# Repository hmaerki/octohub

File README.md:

# octohub

A simple usb 2.0 hub with focus on per port power switching.

Work in progress.

## Features - Hardware

* ~USD 4 when ordering 30 pieces. Fully assembled at JLCPCB.

* Kicad. Production files ready to upload to JLCPCB.

* Power control for each plug using (uhubctl)[https://github.com/mvp/uhubctl].

* **NO** manual power buttons. Many commercial hubs have buttons. If accidentely pressed, usb switching is disabled.

* Power LEDs which are visible from different angles. Many commercial switchs have LEDs, but not well visible.

* Plug numbering. Many commercial switches do not number the plugs and there is very little space left to add stickers.

## Features - Electronics

USB2 only. This makes `uhubctl` much faster.

Bus powered. Less cables is better.

USB descripter `self-powered`. This is against the USB spec. This is required as a RP2 requests 500mA. The USB 2.0 spec allows a bus-powered device to use max 100mA. The current measureed on the RP2 is only 25mA.

Over current protection. However, no over current feedback to USB.

If a device requires USB3, it is still possible to use a commercial hub.

## Current state of v0.2:

[Schematics](octohub_kicad_v0.2/production_v0.2/schematics.pdf)

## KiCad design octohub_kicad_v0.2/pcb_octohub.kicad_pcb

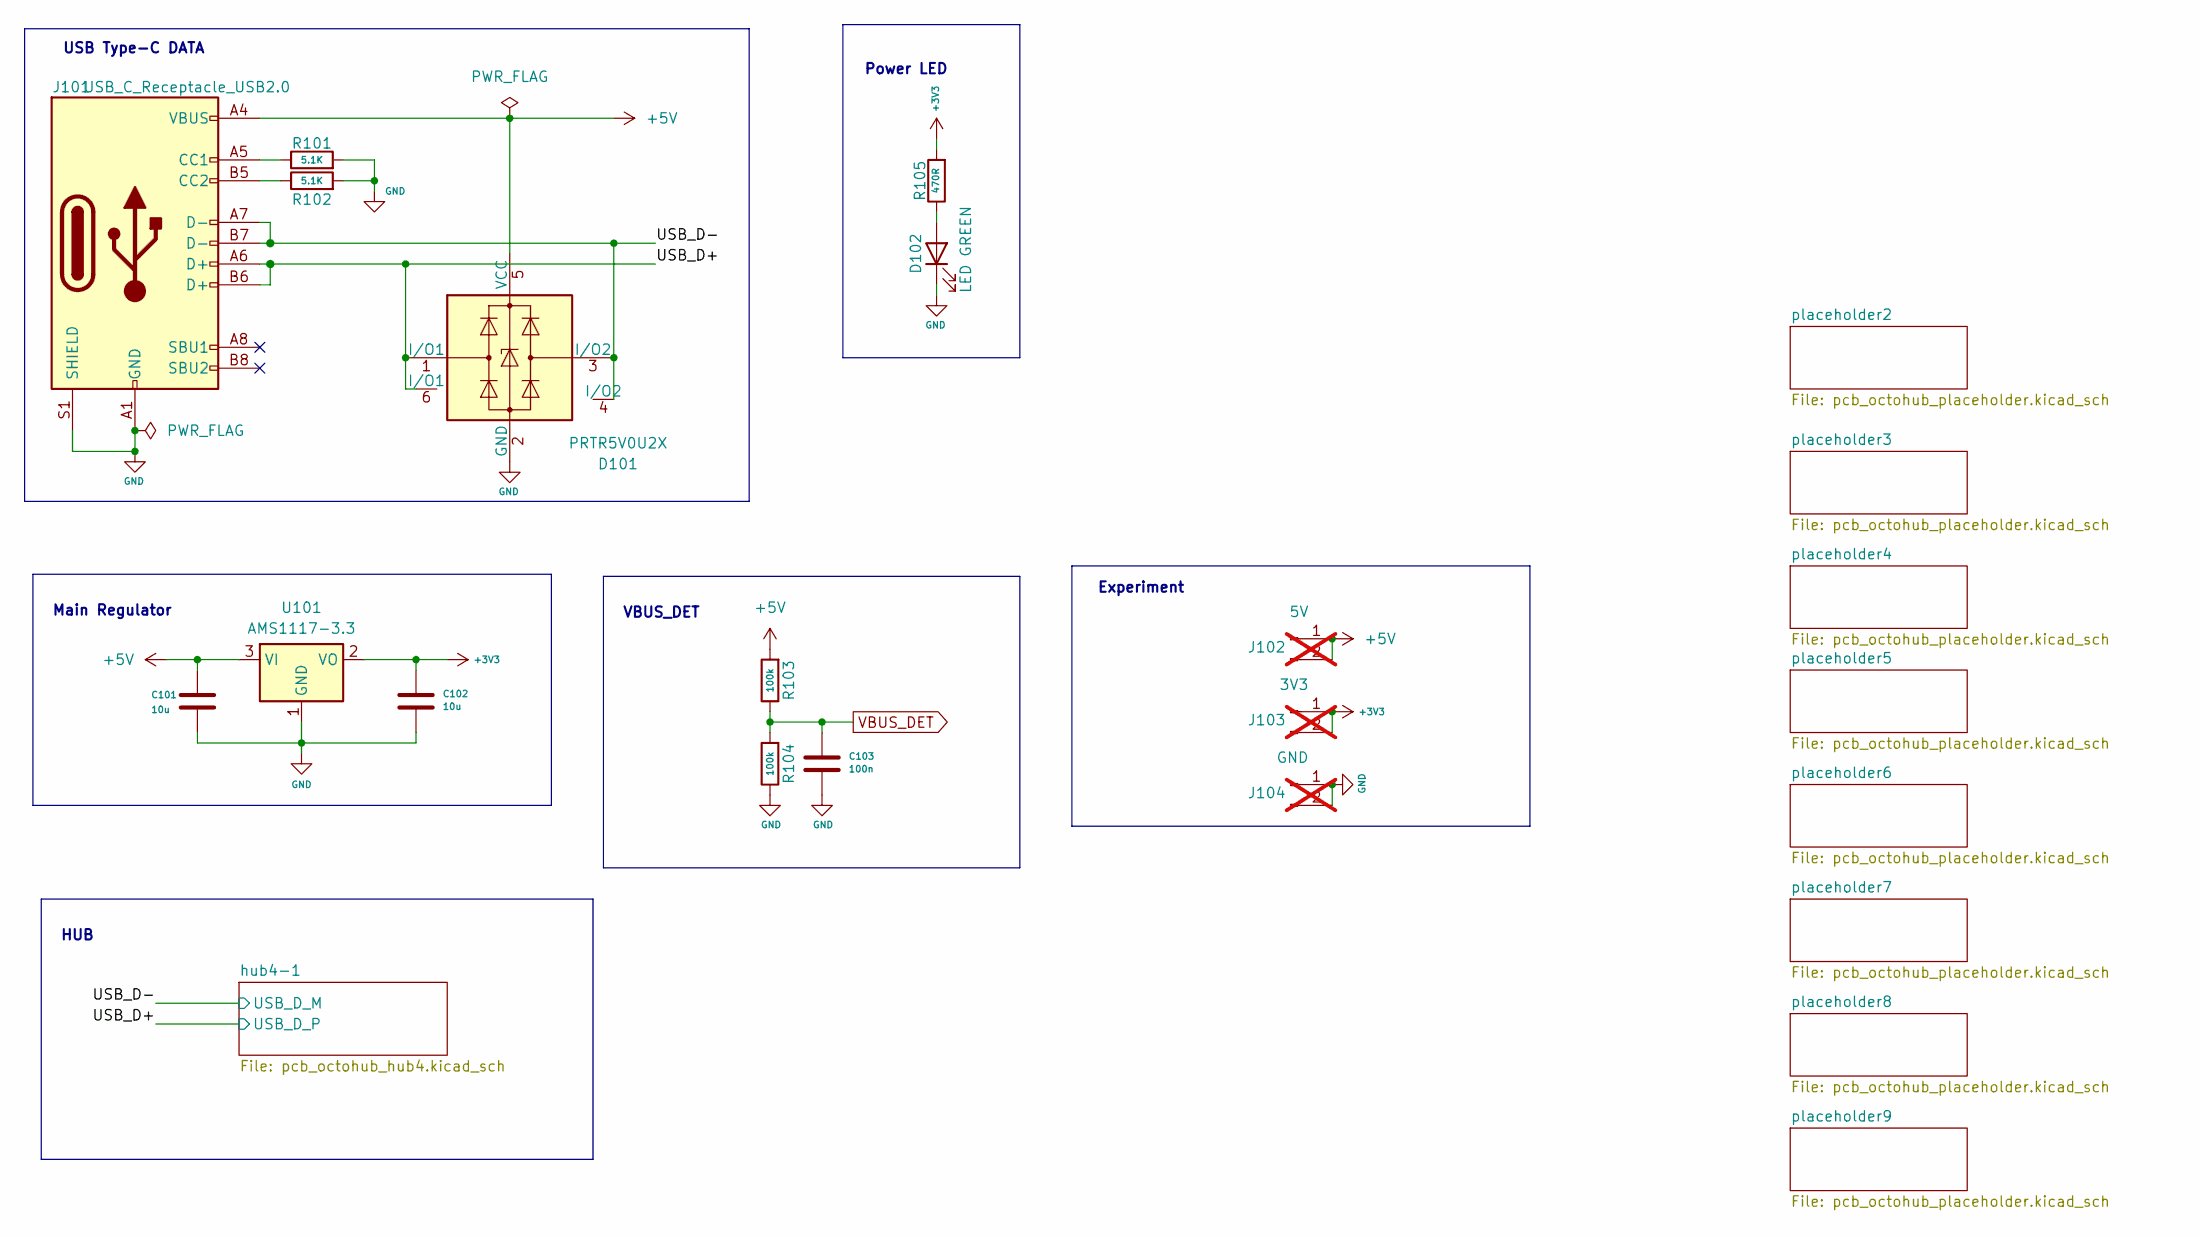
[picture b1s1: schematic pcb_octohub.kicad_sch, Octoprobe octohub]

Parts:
C101, C102: 10u; C_0603_1608Metric
C103: 100n; C_0603_1608Metric
D101: PRTR5V0U2X; Texas_USON-6_1x1.45mm_P0.5mm_SMD; JLC C2937001
D102: LED GREEN; LED_0603_1608Metric; JLC C2297
J101: USB_C_Receptacle_USB2.0; USB_C_Receptacle_Palconn_UTC16-G; JLC C165948
J102: 5V; PinHeader_1x02_P2.54mm_Vertical; not fitted
J103: 3V3; PinHeader_1x02_P2.54mm_Vertical; not fitted
J104: GND; PinHeader_1x02_P2.54mm_Vertical; not fitted
R101, R102: 5.1K; R_0402_1005Metric
R103, R104: 100k; R_0402_1005Metric
R105: 470R; R_0402_1005Metric
U101: AMS1117-3.3; SOT-223-3_TabPin2; JLC C6186

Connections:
+3V3: C102.1, J103.1, J103.2, R105.2, U101.2 (VO); also elsewhere on the board
+5V: C101.1, D101.5 (VCC), J101.A4 (VBUS), J101.A9 (VBUS), J101.B4 (VBUS), J101.B9 (VBUS), J102.1, J102.2, R103.2, U101.3 (VI); also elsewhere on the board
/USB_D+: D101.1 (I/O1), D101.6 (I/O1), J101.A6 (D+), J101.B6 (D+); also elsewhere on the board
/USB_D-: D101.3 (I/O2), D101.4 (I/O2), J101.A7 (D-), J101.B7 (D-); also elsewhere on the board
GND: C101.2, C102.2, C103.2, D101.2 (GND), D102.1 (K), J101.A1 (GND), J101.A12 (GND), J101.B1 (GND), J101.B12 (GND), J101.S1 (SHIELD), J104.1, J104.2, R101.2, R102.2, R104.1, U101.1 (GND); also elsewhere on the board
unnamed: D102.2 (A), R105.1
unnamed: J101.A5 (CC1), R101.1
unnamed: J101.B5 (CC2), R102.1
VBUS_DET: C103.1, R103.1, R104.2; also elsewhere on the board

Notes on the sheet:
USB Type-C DATA
VBUS_DET
Power LED
Main Regulator
HUB
Experiment

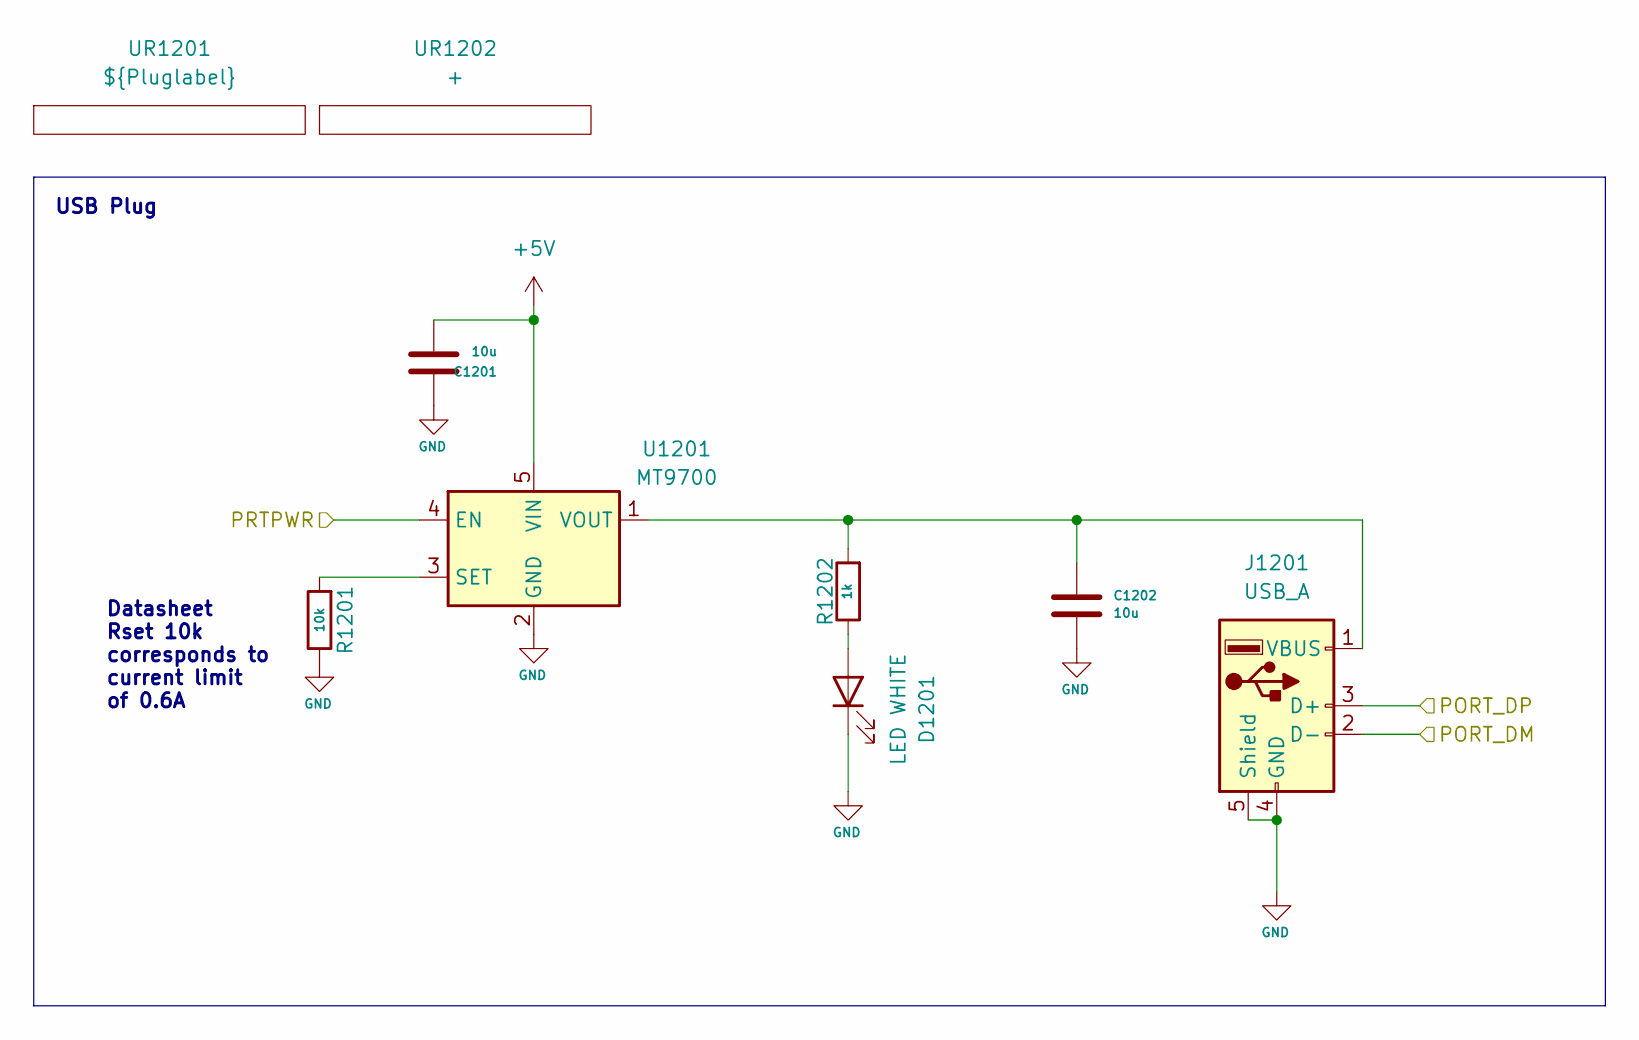
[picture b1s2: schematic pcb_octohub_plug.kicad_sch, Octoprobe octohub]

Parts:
C1201, C1202: 10u; C_0603_1608Metric
D1201: LED WHITE; LED_0603_1608Metric; JLC C2290
J1201: USB_A; USB_A_SHOUHAN_Vertical; JLC C456015
R1201: 10k; R_0402_1005Metric
R1202: 1k; R_0402_1005Metric
U1201: MT9700; SOT-23-5; JLC C89855
UR1201: ${Pluglabel}; octohub_plug_label
UR1202: +; octohub_plug_top_left

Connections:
+5V: C1201.2, U1201.5 (VIN); also elsewhere on the board
/hub4-1/chip_downstream/PRT_D_M1: J1201.2 (D-); also elsewhere on the board
/hub4-1/chip_downstream/PRT_D_P1: J1201.3 (D+); also elsewhere on the board
/hub4-1/chip_downstream/PRT_PWR1: U1201.4 (EN); also elsewhere on the board
GND: C1201.1, C1202.2, D1201.1 (K), J1201.4 (GND), J1201.5 (Shield), R1201.1, U1201.2 (GND); also elsewhere on the board
unnamed: D1201.2 (A), R1202.1
unnamed: C1202.1, J1201.1 (VBUS), R1202.2, U1201.1 (VOUT)
unnamed: R1201.2, U1201.3 (SET)

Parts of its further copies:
C1301, C1302, C1401, C1402, C1501, C1502: 10u; C_0603_1608Metric
D1301, D1401, D1501: LED WHITE; LED_0603_1608Metric; JLC C2290
J1301, J1401, J1501: USB_A; USB_A_SHOUHAN_Vertical; JLC C456015
R1301, R1401, R1501: 10k; R_0402_1005Metric
R1302, R1402, R1502: 1k; R_0402_1005Metric
U1301, U1401, U1501: MT9700; SOT-23-5; JLC C89855
UR1302, UR1402, UR1502: +; octohub_plug_top_left

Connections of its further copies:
+5V: C1301.2, C1401.2, C1501.2, U1301.5 (VIN), U1401.5 (VIN), U1501.5 (VIN); also elsewhere on the board
/hub4-1/chip_downstream/PRT_D_M2: J1301.2 (D-); also elsewhere on the board
/hub4-1/chip_downstream/PRT_D_M3: J1401.3 (D+); also elsewhere on the board
/hub4-1/chip_downstream/PRT_D_M4: J1501.2 (D-); also elsewhere on the board
/hub4-1/chip_downstream/PRT_D_P2: J1301.3 (D+); also elsewhere on the board
/hub4-1/chip_downstream/PRT_D_P3: J1401.2 (D-); also elsewhere on the board
/hub4-1/chip_downstream/PRT_D_P4: J1501.3 (D+); also elsewhere on the board
/hub4-1/chip_downstream/PRT_PWR2: U1301.4 (EN); also elsewhere on the board
/hub4-1/chip_downstream/PRT_PWR3: U1401.4 (EN); also elsewhere on the board
/hub4-1/chip_downstream/PRT_PWR4: U1501.4 (EN); also elsewhere on the board
GND: C1301.1, C1302.2, C1401.1, C1402.2, C1501.1, C1502.2, D1301.1 (K), D1401.1 (K), D1501.1 (K), J1301.4 (GND), J1301.5 (Shield), J1401.4 (GND), J1401.5 (Shield), J1501.4 (GND), J1501.5 (Shield), R1301.1, R1401.1, R1501.1, U1301.2 (GND), U1401.2 (GND), U1501.2 (GND); also elsewhere on the board
unnamed: D1301.2 (A), R1302.1
unnamed: D1401.2 (A), R1402.1
unnamed: D1501.2 (A), R1502.1
unnamed: C1302.1, J1301.1 (VBUS), R1302.2, U1301.1 (VOUT)
unnamed: C1402.1, J1401.1 (VBUS), R1402.2, U1401.1 (VOUT)
unnamed: C1502.1, J1501.1 (VBUS), R1502.2, U1501.1 (VOUT)
unnamed: R1301.2, U1301.3 (SET)
unnamed: R1401.2, U1401.3 (SET)
unnamed: R1501.2, U1501.3 (SET)

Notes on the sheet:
USB Plug
Datasheet Rset 10k corresponds to current limit of 0.6A

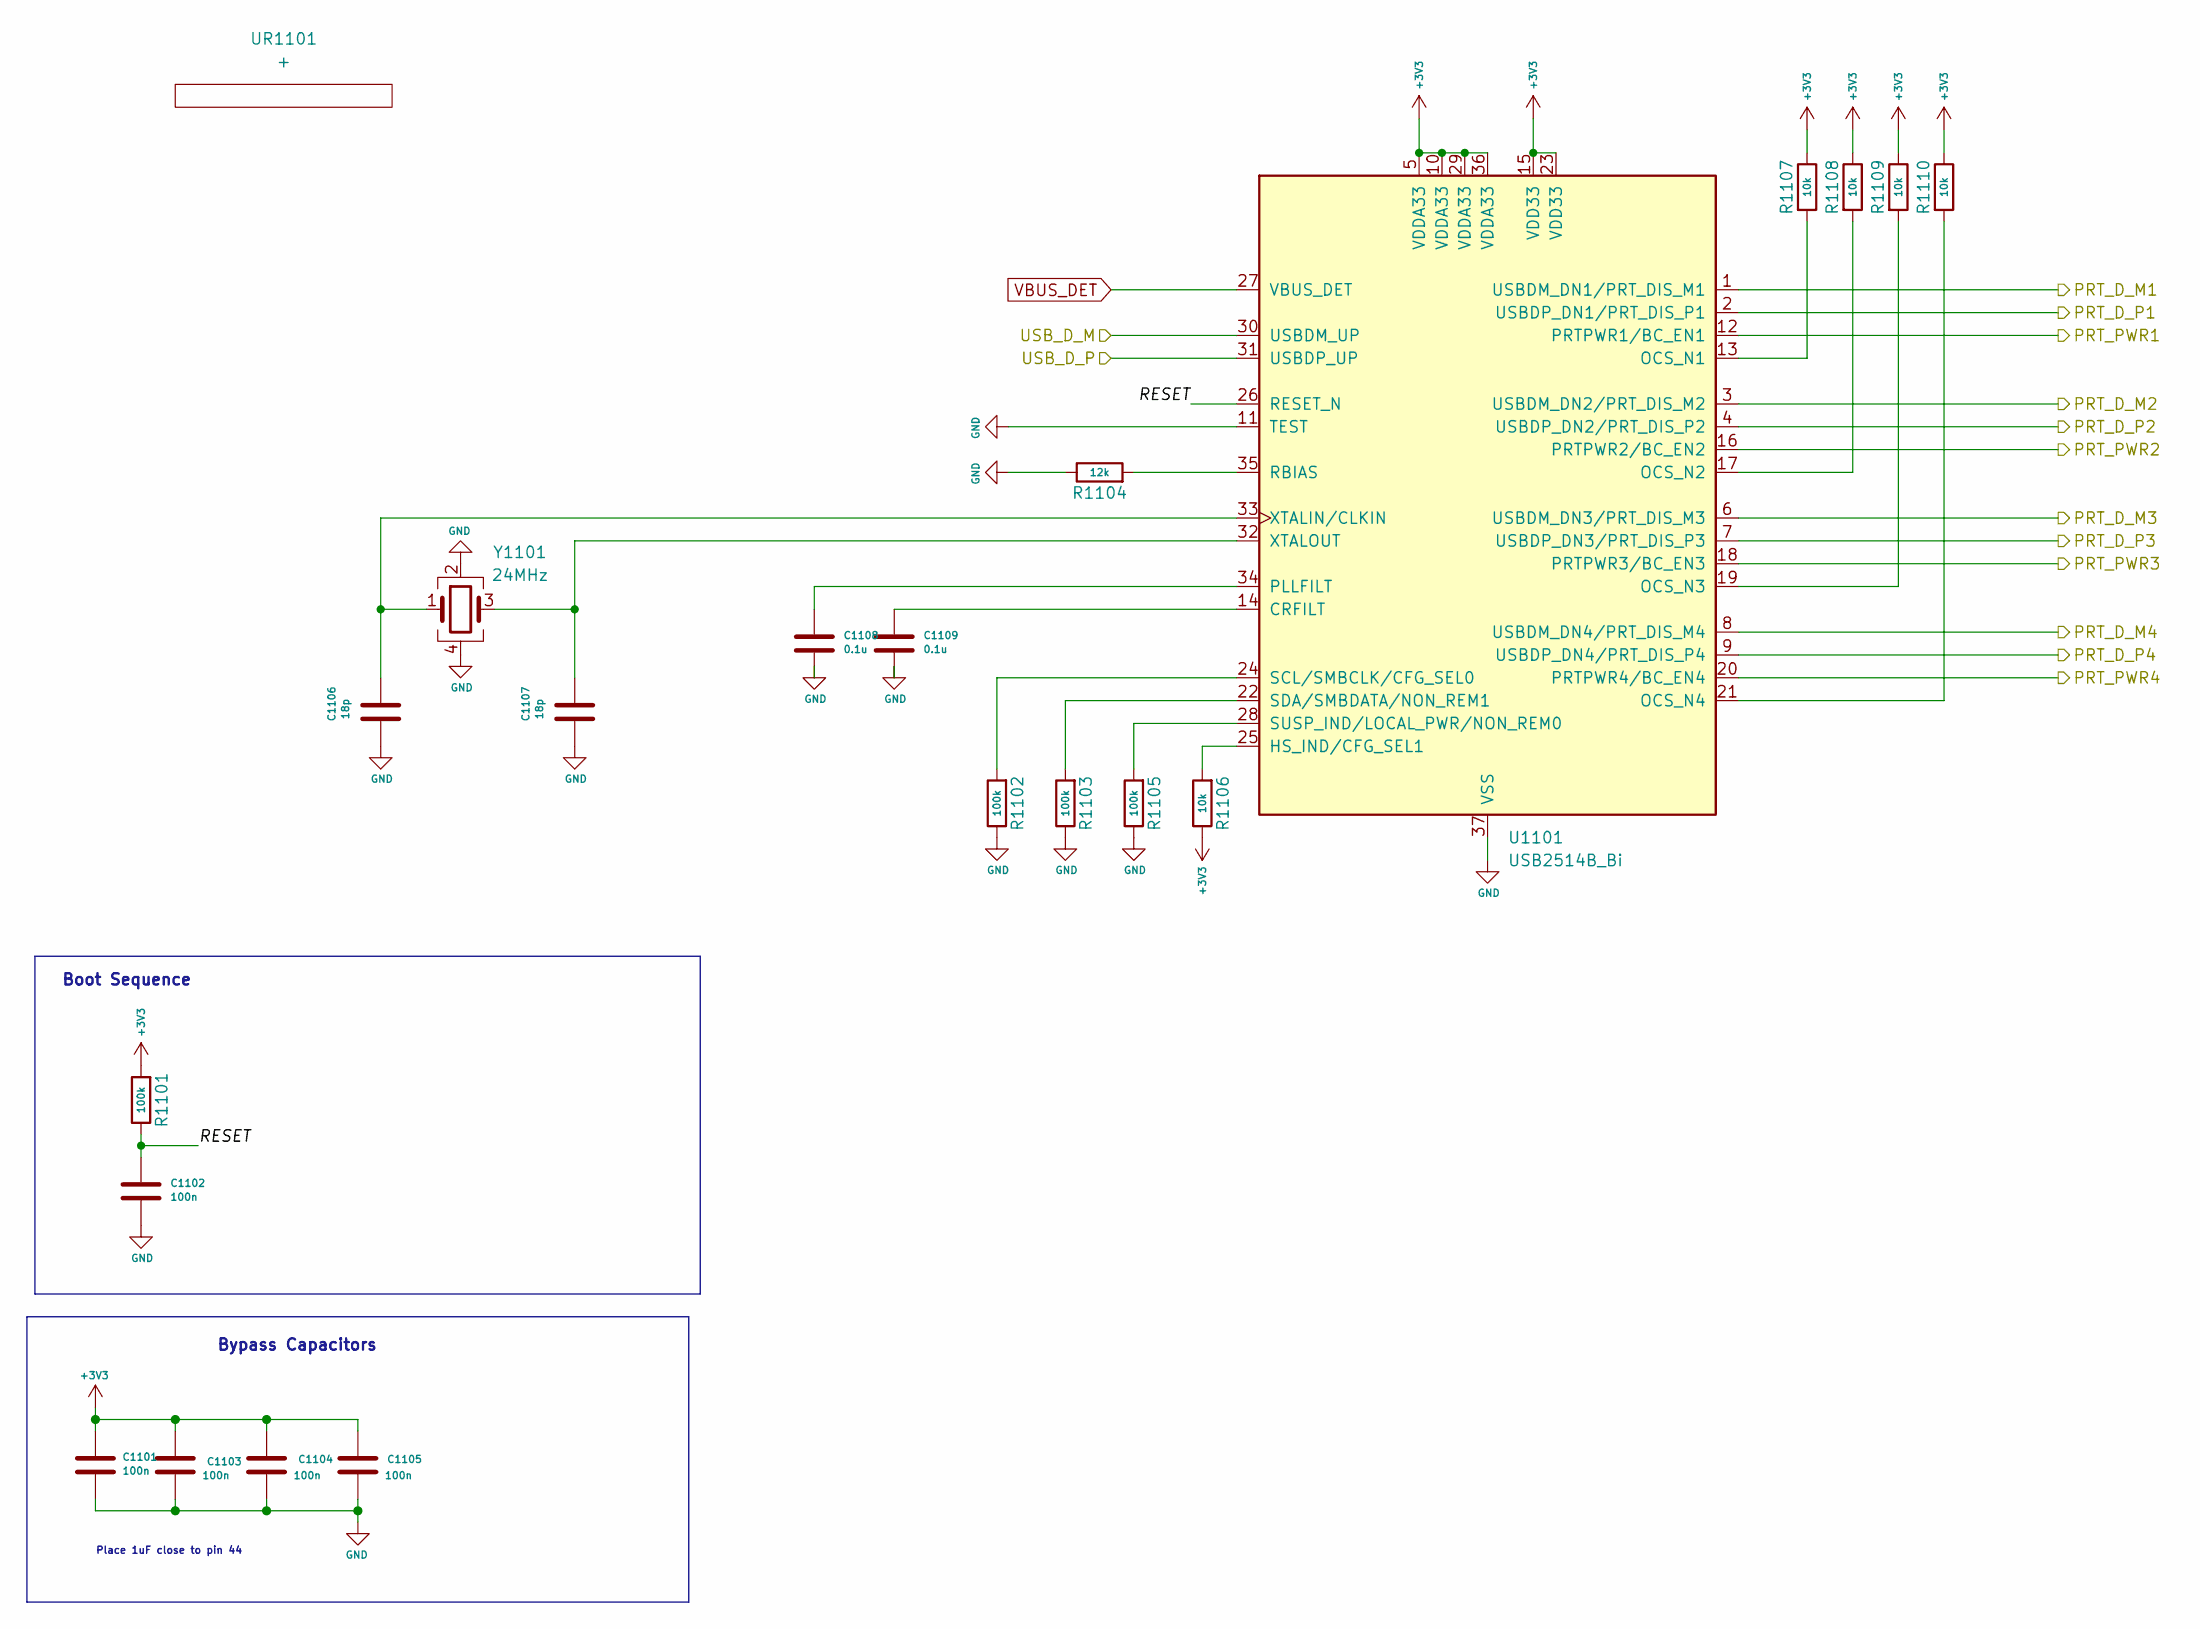
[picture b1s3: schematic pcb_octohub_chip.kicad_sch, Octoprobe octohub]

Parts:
C1101, C1103, C1104, C1105: 100n; C_0402_1005Metric
C1102: 100n; C_0603_1608Metric
C1106, C1107: 18p; C_0805_2012Metric; JLC C1797
C1108, C1109: 0.1u; C_0402_1005Metric
R1101, R1102, R1103, R1105: 100k; R_0402_1005Metric
R1104: 12k; R_0402_1005Metric
R1106, R1107, R1108, R1109, R1110: 10k; R_0402_1005Metric
U1101: USB2514B_Bi; Texas_RHH0036C_VQFN-36-1EP_6x6mm_P0.5mm_EP4.4x4.4mm_Thermal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; JLC C16251
UR1101: +; octohub_plug_top_left
Y1101: 24MHz; Crystal_SMD_3225-4Pin_3.2x2.5mm; JLC C70590

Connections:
+3V3: C1101.1, C1103.1, C1104.1, C1105.1, R1101.2, R1106.1, R1107.1, R1108.1, R1109.1, R1110.1, U1101.5 (VDDA33), U1101.10 (VDDA33), U1101.15 (VDD33), U1101.23 (VDD33), U1101.29 (VDDA33), U1101.36 (VDDA33); also elsewhere on the board
/USB_D+: U1101.31 (USBDP_UP); also elsewhere on the board
/USB_D-: U1101.30 (USBDM_UP); also elsewhere on the board
/hub4-1/chip_downstream/PRT_D_M1: U1101.1 (USBDM_DN1/PRT_DIS_M1); also elsewhere on the board
/hub4-1/chip_downstream/PRT_D_M2: U1101.3 (USBDM_DN2/PRT_DIS_M2); also elsewhere on the board
/hub4-1/chip_downstream/PRT_D_M3: U1101.6 (USBDM_DN3/PRT_DIS_M3); also elsewhere on the board
/hub4-1/chip_downstream/PRT_D_M4: U1101.8 (USBDM_DN4/PRT_DIS_M4); also elsewhere on the board
/hub4-1/chip_downstream/PRT_D_P1: U1101.2 (USBDP_DN1/PRT_DIS_P1); also elsewhere on the board
/hub4-1/chip_downstream/PRT_D_P2: U1101.4 (USBDP_DN2/PRT_DIS_P2); also elsewhere on the board
/hub4-1/chip_downstream/PRT_D_P3: U1101.7 (USBDP_DN3/PRT_DIS_P3); also elsewhere on the board
/hub4-1/chip_downstream/PRT_D_P4: U1101.9 (USBDP_DN4/PRT_DIS_P4); also elsewhere on the board
/hub4-1/chip_downstream/PRT_PWR1: U1101.12 (PRTPWR1/BC_EN1); also elsewhere on the board
/hub4-1/chip_downstream/PRT_PWR2: U1101.16 (PRTPWR2/BC_EN2); also elsewhere on the board
/hub4-1/chip_downstream/PRT_PWR3: U1101.18 (PRTPWR3/BC_EN3); also elsewhere on the board
/hub4-1/chip_downstream/PRT_PWR4: U1101.20 (PRTPWR4/BC_EN4); also elsewhere on the board
/hub4-1/chip_downstream/RESET: C1102.1, R1101.1, U1101.26 (RESET_N)
GND: C1101.2, C1102.2, C1103.2, C1104.2, C1105.2, C1106.2, C1107.2, C1108.2, C1109.2, R1102.1, R1103.1, R1104.1, R1105.1, U1101.11 (TEST), U1101.37 (VSS), Y1101.2, Y1101.4; also elsewhere on the board
unnamed: C1109.1, U1101.14 (CRFILT)
unnamed: R1106.2, U1101.25 (HS_IND/CFG_SEL1)
unnamed: R1107.2, U1101.13 (OCS_N1)
unnamed: R1108.2, U1101.17 (OCS_N2)
unnamed: R1109.2, U1101.19 (OCS_N3)
unnamed: R1110.2, U1101.21 (OCS_N4)
unnamed: C1108.1, U1101.34 (PLLFILT)
unnamed: R1104.2, U1101.35 (RBIAS)
unnamed: R1102.2, U1101.24 (SCL/SMBCLK/CFG_SEL0)
unnamed: R1103.2, U1101.22 (SDA/SMBDATA/NON_REM1)
unnamed: R1105.2, U1101.28 (SUSP_IND/LOCAL_PWR/NON_REM0)
unnamed: C1106.1, U1101.33 (XTALIN/CLKIN), Y1101.1
unnamed: C1107.1, U1101.32 (XTALOUT), Y1101.3
VBUS_DET: U1101.27 (VBUS_DET); also elsewhere on the board

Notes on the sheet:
Place 1uF close to pin 44
Bypass Capacitors
Boot Sequence

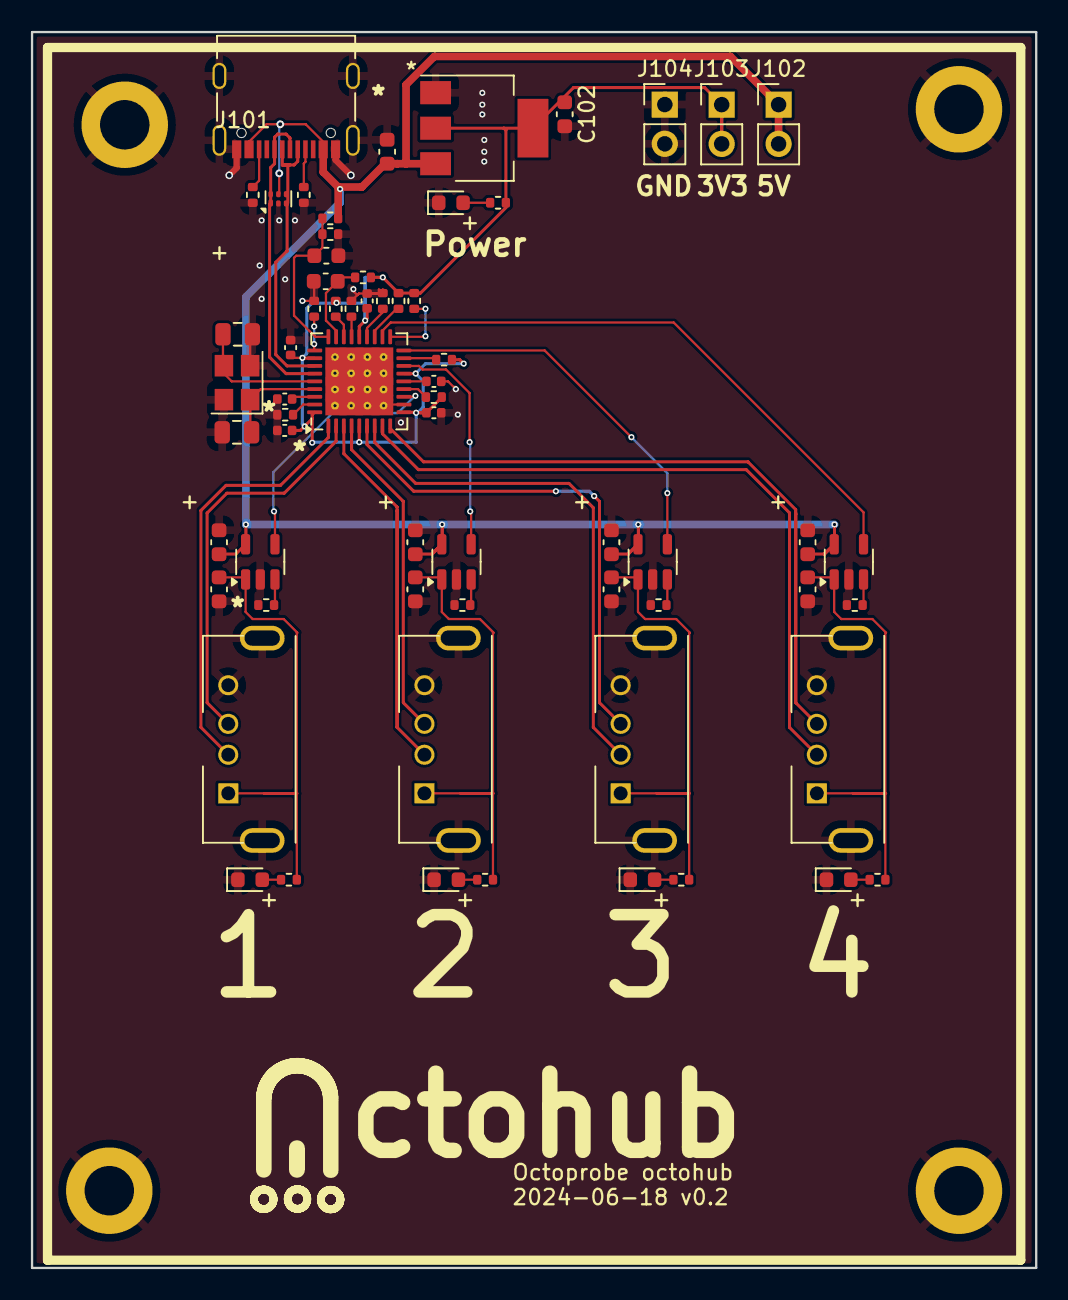
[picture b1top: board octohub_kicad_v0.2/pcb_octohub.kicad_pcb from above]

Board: 2 copper layers, 65.0 x 80.0 mm, 77 parts (0 on the bottom side), 47 nets.

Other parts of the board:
H101, H102, H103, H104: octoprobe_MountingHole; MountingHole_3.2mm_M3_DIN965_Pad
UR1301: 2; octohub_plug_label
UR1401: 3; octohub_plug_label
UR1501: 4; octohub_plug_label

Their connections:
GND: H101.1, H102.1, H103.1, H104.1; also elsewhere on the board

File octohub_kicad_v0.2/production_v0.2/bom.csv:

Designator,Footprint,Quantity,Value,LCSC Part #
"C101, C102, C1201, C1202, C1301, C1302, C1401, C1402, C1501, C1502",0603,10,10u,
"C103, C1102",0603,2,100n,
"C1101, C1103, C1104, C1105",0402,4,100n,
"C1106, C1107",0805,2,18p,C1797
"C1108, C1109",0402,2,0.1u,
D101,Texas_USON-6_1x1.45mm_P0.5mm_SMD,1,PRTR5V0U2X,C2937001
D102,0603,1,LED GREEN,C2297
"D1201, D1301, D1401, D1501",0603,4,LED WHITE,C2290
"H101, H102, H103, H104",MountingHole_3.2mm_M3_DIN965_Pad,4,octoprobe_MountingHole,
J101,USB_C_Receptacle_Palconn_UTC16-G,1,USB_C_Receptacle_USB2.0,C165948
"J1201, J1301, J1401, J1501",USB_A_SHOUHAN_Vertical,4,USB_A,C456015
"R101, R102",0402,2,5.1K,
"R103, R104, R1101, R1102, R1103, R1105",0402,6,100k,
R105,0402,1,470R,
R1104,0402,1,12k,
"R1106, R1107, R1108, R1109, R1110, R1201, R1301, R1401, R1501",0402,9,10k,
"R1202, R1302, R1402, R1502",0402,4,1k,
U101,SOT-223-3_TabPin2,1,AMS1117-3.3,C6186
U1101,Texas_RHH0036C_VQFN-36-1EP_6x6mm_P0.5mm_EP4.4x4.4mm_ThermalVias,1,USB2514B_Bi,C16251
"U1201, U1301, U1401, U1501",SOT-23-5,4,MT9700,C89855
Y1101,Crystal_SMD_3225-4Pin_3.2x2.5mm,1,24MHz,C70590

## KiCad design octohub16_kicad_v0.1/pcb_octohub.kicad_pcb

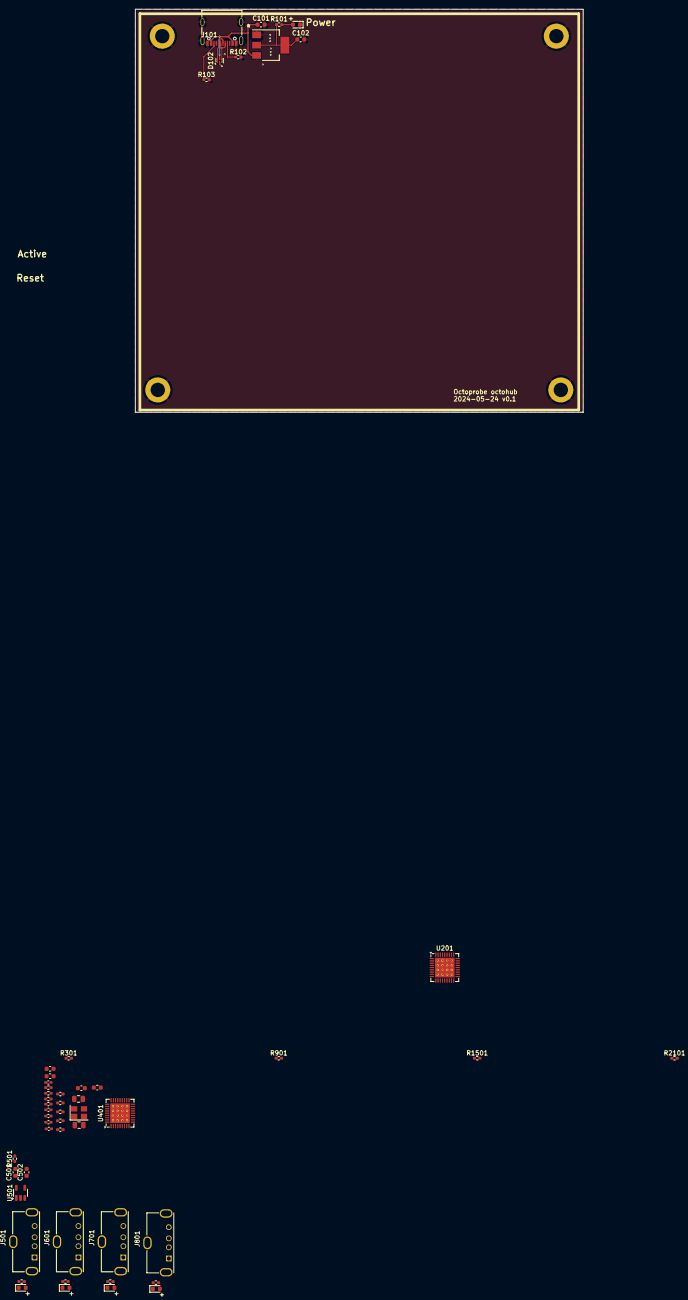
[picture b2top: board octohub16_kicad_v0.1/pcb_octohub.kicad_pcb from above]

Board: 2 copper layers, 100.0 x 90.0 mm, 56 parts (0 on the bottom side), 39 nets.

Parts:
C101, C102, C501, C502: 10u; C_0603_1608Metric
C401: 1u; C_0402_1005Metric_Pad0.74x0.62mm_HandSolder
C402, C411, C412: 0.1u; C_0603_1608Metric
C403, C404, C405, C407, C409: 100n; C_0402_1005Metric_Pad0.74x0.62mm_HandSolder
C406: 1n; C_0603_1608Metric
C408, C410: 18p; C_0805_2012Metric
D101: LED GREEN; LED_0603_1608Metric
D102: PRTR5V0U2X; Texas_USON-6_1x1.45mm_P0.5mm_SMD
D501, D601, D701, D801: LED WHITE; LED_0603_1608Metric
H101, H102, H103, H104: octoprobe_MountingHole; MountingHole_3.2mm_M3_DIN965_Pad
J101: USB_C_Receptacle_USB2.0; USB_C_Receptacle_Palconn_UTC16-G
J501, J601, J701, J801: USB_A; USB_A_Molex_105057_Vertical
R101, R502, R602, R702, R802: 470R; R_0402_1005Metric_Pad0.72x0.64mm_HandSolder
R102, R103: 5.1K; R_0402_1005Metric_Pad0.72x0.64mm_HandSolder
R301, R401, R402, R403, R404, R405, R406, R407, R901, R1501, R2101: 100k; R_0402_1005Metric_Pad0.72x0.64mm_HandSolder
R408: 12k; R_0402_1005Metric_Pad0.72x0.64mm_HandSolder
R501: 10k; R_0402_1005Metric_Pad0.72x0.64mm_HandSolder
U101: AMS1117-3.3; SOT-223-3_TabPin2
U201, U401: USB2514B_Bi; Texas_RHH0036C_VQFN-36-1EP_6x6mm_P0.5mm_EP4.4x4.4mm_Thermal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
U501: MT9700; SOT-23-5
Y401: 24MHz; Crystal_SMD_3225-4Pin_3.2x2.5mm

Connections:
+3V3: C102.1, C401.1, C403.1, C404.1, C405.1, C407.1, C409.1, R101.2, R301.2, R401.2, R406.1, R407.1, R901.2, R1501.2, R2101.2, U101.2 (VO), U201.5 (VDDA33), U201.10 (VDDA33), U201.15 (VDD33), U201.23 (VDD33), U201.29 (VDDA33), U201.36 (VDDA33), U401.5 (VDDA33), U401.10 (VDDA33), U401.15 (VDD33), U401.23 (VDD33), U401.29 (VDDA33), U401.36 (VDDA33)
+5V: C101.1, C501.2, D102.5 (VCC), J101.A4 (VBUS), J101.A9 (VBUS), J101.B4 (VBUS), J101.B9 (VBUS), R402.2, U101.3 (VI), U501.5 (VIN)
/chip_upstream/PRT_M1: U201.1 (USBDM_DN1/PRT_DIS_M1), U401.30 (USBDM_UP)
/chip_upstream/PRT_P1: U201.2 (USBDP_DN1/PRT_DIS_P1), U401.31 (USBDP_UP)
/chip_upstream/USB_DM: D102.3 (I/O2), D102.4 (I/O2), J101.A7 (D-), J101.B7 (D-), U201.30 (USBDM_UP)
/chip_upstream/USB_DP: D102.1 (I/O1), D102.6 (I/O1), J101.A6 (D+), J101.B6 (D+), U201.31 (USBDP_UP)
/hub4-1/chip_downstream/PRTPWR1: U401.12 (PRTPWR1/BC_EN1), U501.4 (EN)
/hub4-1/chip_downstream/PRT_M1: J501.2 (D-), U401.1 (USBDM_DN1/PRT_DIS_M1)
/hub4-1/chip_downstream/PRT_M2: J601.2 (D-), U401.3 (USBDM_DN2/PRT_DIS_M2)
/hub4-1/chip_downstream/PRT_M3: J701.2 (D-), U401.6 (USBDM_DN3/PRT_DIS_M3)
/hub4-1/chip_downstream/PRT_M4: J801.2 (D-), U401.8 (USBDM_DN4/PRT_DIS_M4)
/hub4-1/chip_downstream/PRT_P1: J501.3 (D+), U401.2 (USBDP_DN1/PRT_DIS_P1)
/hub4-1/chip_downstream/PRT_P2: J601.3 (D+), U401.4 (USBDP_DN2/PRT_DIS_P2)
/hub4-1/chip_downstream/PRT_P3: J701.3 (D+), U401.7 (USBDP_DN3/PRT_DIS_P3)
/hub4-1/chip_downstream/PRT_P4: J801.3 (D+), U401.9 (USBDP_DN4/PRT_DIS_P4)
/hub4-1/chip_downstream/RESET: C402.1, R401.1, U401.26 (RESET_N)
/hub4-1/chip_downstream/VBUS_DET: C406.1, R402.1, R403.2, U401.27 (VBUS_DET)
GND: C101.2, C102.2, C401.2, C402.2, C403.2, C404.2, C405.2, C406.2, C407.2, C408.2, C409.2, C410.2, C411.2, C412.2, C501.1, C502.2, D101.1 (K), D102.2 (GND), D501.1 (K), D601.1 (K), D701.1 (K), D801.1 (K), H101.1, H102.1, H103.1, H104.1, J101.A1 (GND), J101.A12 (GND), J101.B1 (GND), J101.B12 (GND), J101.S1 (SHIELD), J501.4 (GND), J601.4 (GND), J701.4 (GND), J801.4 (GND), R102.2, R103.2, R301.1, R403.1, R404.1, R405.1, R408.1, R501.1, R901.1, R1501.1, R2101.1, U101.1 (GND), U201.11 (TEST), U201.37 (VSS), U401.11 (TEST), U401.37 (VSS), U501.2 (GND), Y401.2, Y401.4
unnamed: D101.2 (A), R101.1
unnamed: D501.2 (A), R502.1
unnamed: D601.2 (A), R602.1
unnamed: D701.2 (A), R702.1
unnamed: D801.2 (A), R802.1
unnamed: J101.A5 (CC1), R102.1
unnamed: J101.B5 (CC2), R103.1
unnamed: C502.1, J501.1 (VBUS), R502.2, U501.1 (VOUT)
unnamed: J601.1 (VBUS), R602.2
unnamed: J701.1 (VBUS), R702.2
unnamed: J801.1 (VBUS), R802.2
unnamed: C412.1, U401.14 (CRFILT)
unnamed: R407.2, U401.25 (HS_IND/CFG_SEL1)
unnamed: C411.1, U401.34 (PLLFILT)
unnamed: R408.2, U401.35 (RBIAS)
unnamed: R404.2, U401.24 (SCL/SMBCLK/CFG_SEL0)
unnamed: R405.2, U401.22 (SDA/SMBDATA/NON_REM1)
unnamed: R406.2, U401.28 (SUSP_IND/LOCAL_PWR/NON_REM0)
unnamed: C408.1, U401.33 (XTALIN/CLKIN), Y401.1
unnamed: C410.1, U401.32 (XTALOUT), Y401.3
unnamed: R501.2, U501.3 (SET)

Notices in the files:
octohub16_kicad_v0.1/pcb_octohub.kicad_pcb:
The MIT License (MIT)
